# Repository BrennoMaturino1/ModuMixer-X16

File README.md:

# ModuMixer X16
ModuMixer is a modular digital audio mixer project with an almost unlimited amount of input and output channels (the limit is 65536)
It can be customized with input or output modules that are recognized by the "main computer"
The cue and main output signals are connected together in a summing amplifier configuration where each module sums it's signal to the data lines
The modules are digitally recognized by a custom protocol over USART where during boot one module is powered at a time and receives an address from the main computer (i know connecting multiple devices to USART isn't a good idea but i guess it will work), the digital signal processing works with an STM32 microcontroller for processing and a codec for digital to analog and analog to digital conversions

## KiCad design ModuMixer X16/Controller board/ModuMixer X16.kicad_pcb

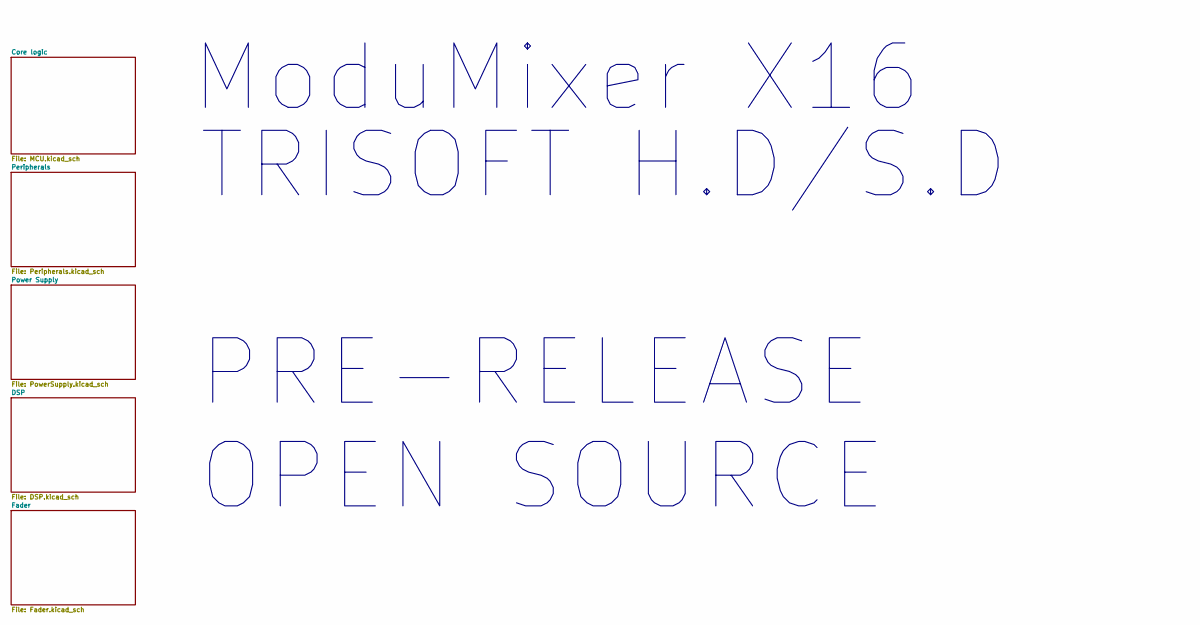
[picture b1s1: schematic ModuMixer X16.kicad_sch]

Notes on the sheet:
ModuMixer X16
TRISOFT H.D/S.D PRE-RELEASE OPEN SOURCE

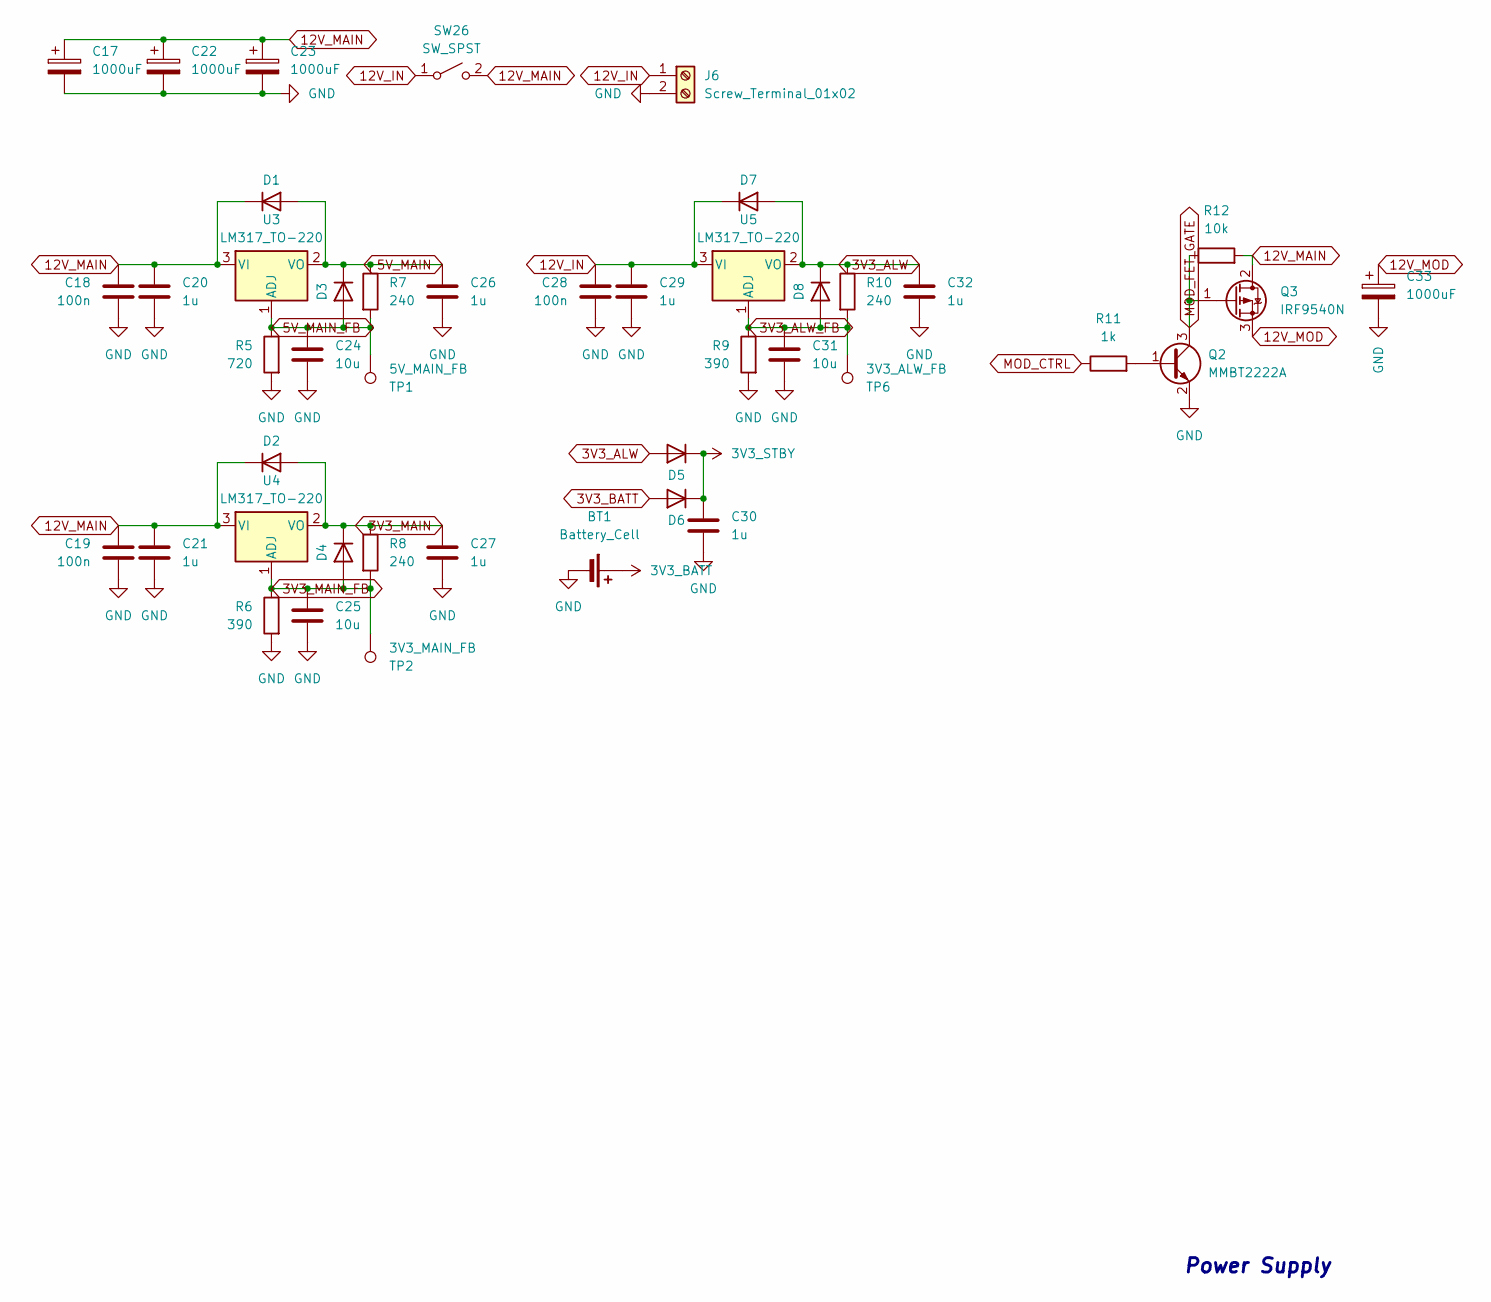
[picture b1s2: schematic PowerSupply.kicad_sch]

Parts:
BT1: Battery_Cell
C17, C22, C23, C33: 1000uF; CP_Elec_10x10
C18, C19, C28: 100n; C_0603_1608Metric
C20, C21, C26, C27, C29, C30, C32: 1u; C_0603_1608Metric
C24, C25, C31: 10u; C_0603_1608Metric
D1, D2, D3, D4, D5, D6, D7, D8: D_SOD-123
J6: Screw_Terminal_01x02; TerminalBlock_Xinya_XY308-2.54-2P_1x02_P2.54mm_Horizontal
Q2: MMBT2222A; SOT-23
Q3: IRF9540N; TO-220-3_Vertical
R5: 720; R_0603_1608Metric
R6, R9: 390; R_0603_1608Metric
R7, R8, R10: 240; R_0603_1608Metric
R11: 1k; R_0603_1608Metric
R12: 10k; R_0603_1608Metric
SW26: SW_SPST; TerminalBlock_Xinya_XY308-2.54-2P_1x02_P2.54mm_Horizontal
TP1: 5V_MAIN_FB; TestPoint_Pad_D3.0mm
TP2: 3V3_MAIN_FB; TestPoint_Pad_D3.0mm
TP6: 3V3_ALW_FB; TestPoint_Pad_D3.0mm
U3, U4, U5: LM317_TO-220; TO-220-3_Vertical

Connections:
3V3_ALW: C32.1, D5.2 (A), D7.2 (A), D8.1 (K), R10.1, U5.2 (VO)
3V3_ALW_FB: C31.1, D8.2 (A), R9.1, R10.2, TP6.1, U5.1 (ADJ)
3V3_BATT: D6.2 (A)
3V3_MAIN: C27.1, D2.2 (A), D4.1 (K), R8.1, U4.2 (VO); also elsewhere on the board
3V3_MAIN_FB: C25.1, D4.2 (A), R6.1, R8.2, TP2.1, U4.1 (ADJ)
3V3_STBY: C30.1, D5.1 (K), D6.1 (K); also elsewhere on the board
5V_MAIN: C26.1, D1.2 (A), D3.1 (K), R7.1, U3.2 (VO); also elsewhere on the board
5V_MAIN_FB: C24.1, D3.2 (A), R5.1, R7.2, TP1.1, U3.1 (ADJ)
12V_IN: C28.1, C29.1, D7.1 (K), J6.1, SW26.1 (A), U5.3 (VI)
12V_MAIN: C17.1, C18.1, C19.1, C20.1, C21.1, C22.1, C23.1, D1.1 (K), D2.1 (K), Q3.2 (D), R12.2, SW26.2 (B), U3.3 (VI), U4.3 (VI)
12V_MOD: C33.1, Q3.3 (S); also elsewhere on the board
GND: BT1.2 (-), C17.2, C18.2, C19.2, C20.2, C21.2, C22.2, C23.2, C24.2, C25.2, C26.2, C27.2, C28.2, C29.2, C30.2, C31.2, C32.2, C33.2, J6.2, Q2.2 (E), R5.2, R6.2, R9.2; also elsewhere on the board
MOD_CTRL: R11.1; also elsewhere on the board
MOD_FET_GATE: Q2.3 (C), Q3.1 (G), R12.1
unnamed: Q2.1 (B), R11.2

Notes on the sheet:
Power Supply

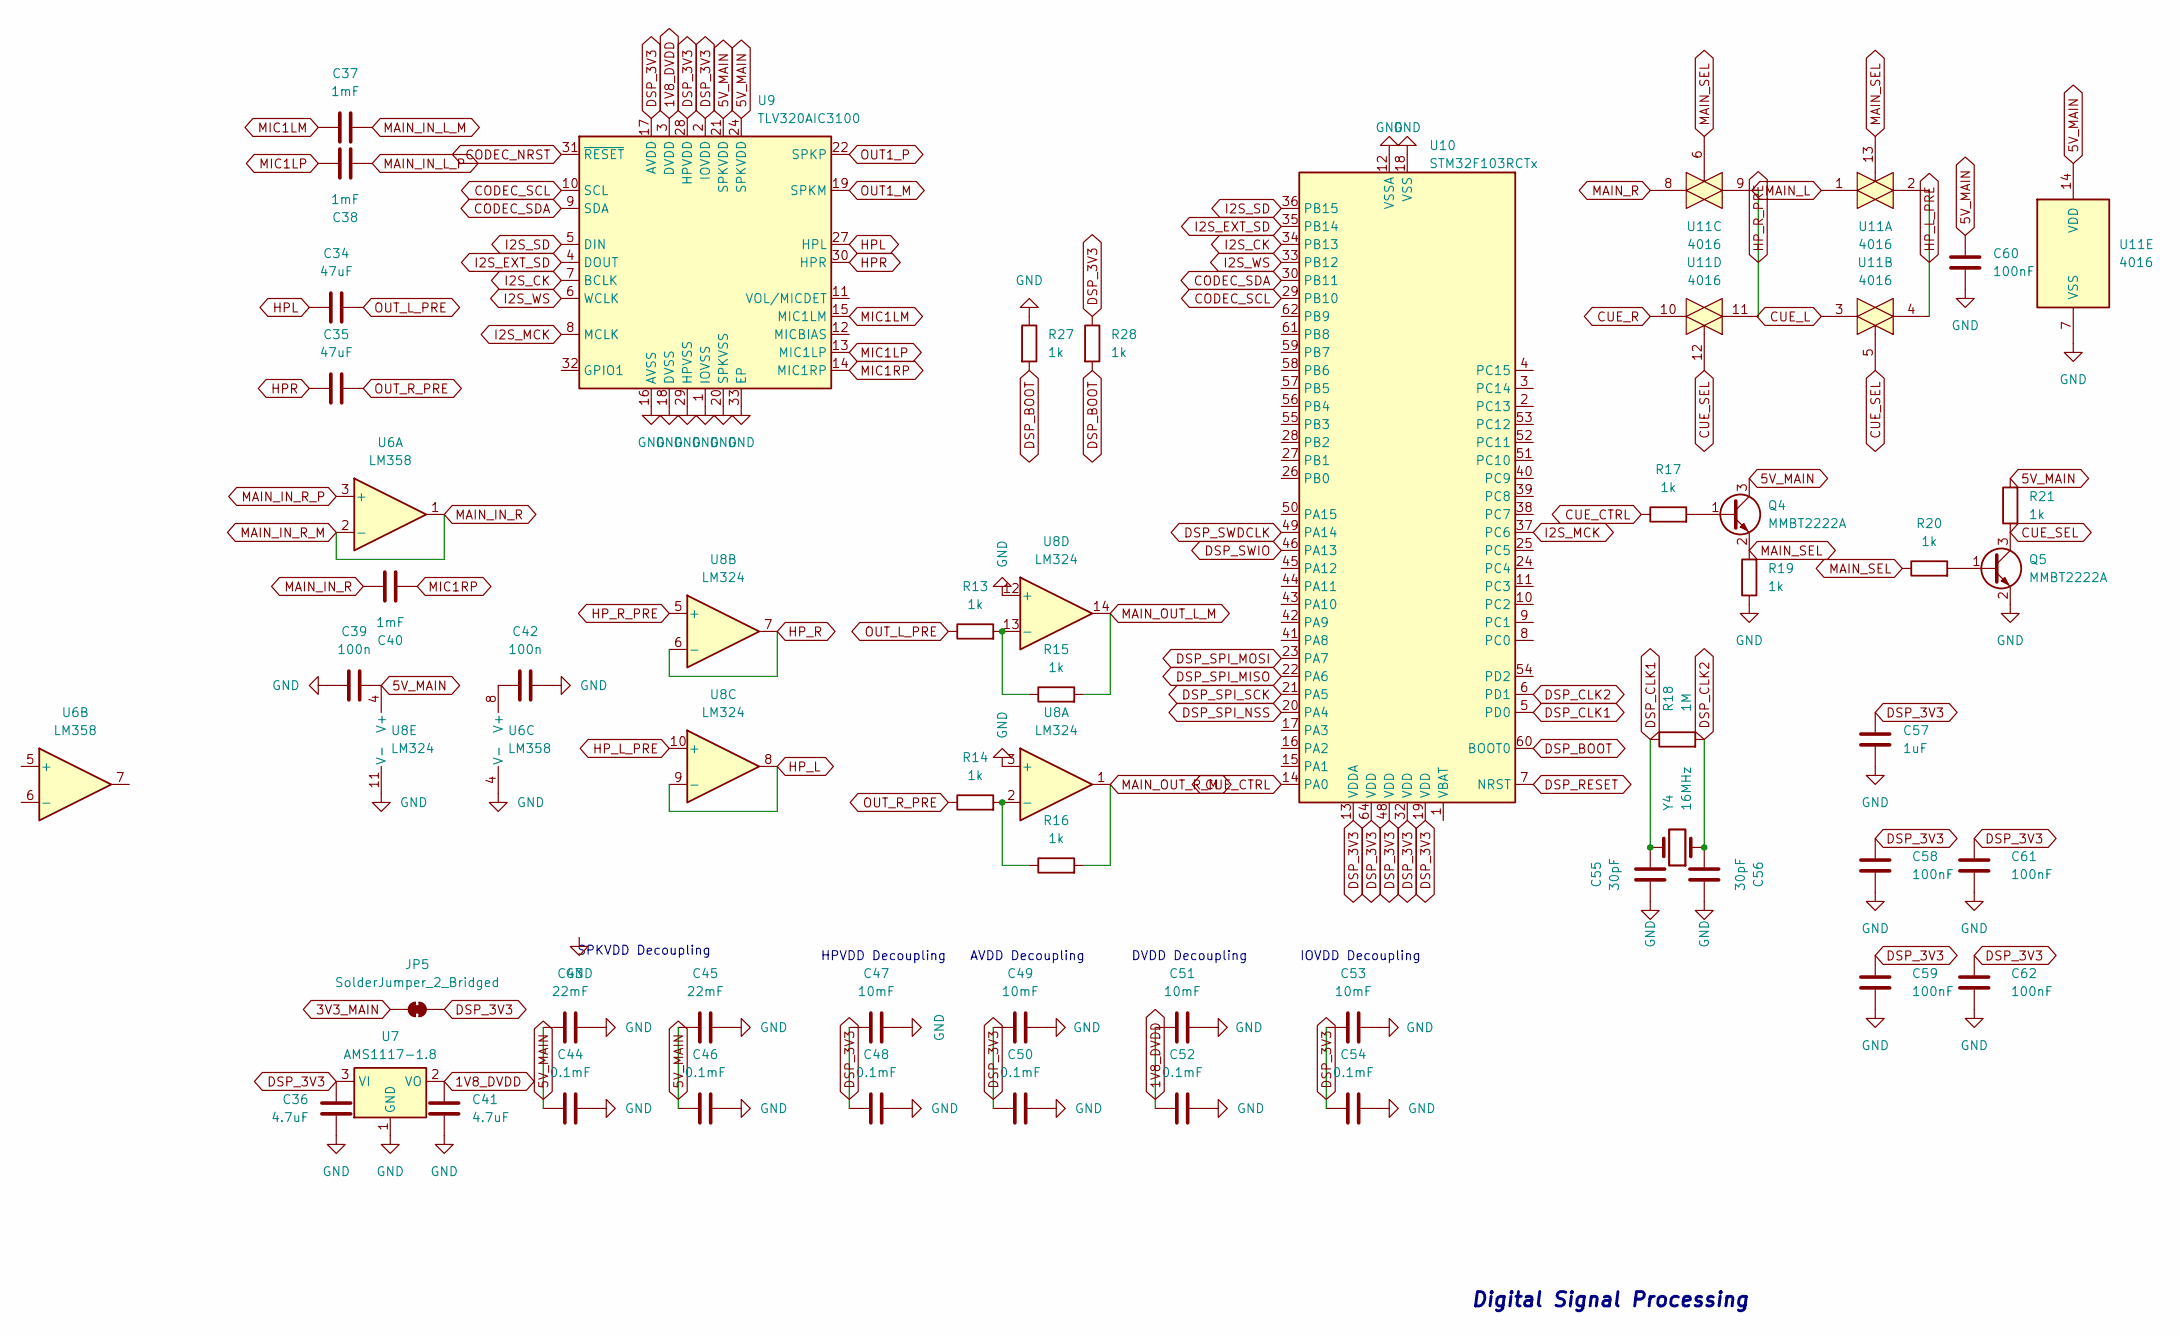
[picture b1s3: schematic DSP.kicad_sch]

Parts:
C34, C35: 47uF; C_0603_1608Metric
C36, C41: 4.7uF; C_0603_1608Metric
C37, C38, C40: 1mF; C_0603_1608Metric
C39, C42: 100n; C_0603_1608Metric
C43, C45: 22mF; C_0603_1608Metric
C44, C46, C48, C50, C52, C54: 0.1mF; C_0603_1608Metric
C47, C49, C51, C53: 10mF; C_0603_1608Metric
C55, C56: 30pF; C_0603_1608Metric
C57: 1uF; C_0603_1608Metric
C58, C59, C60, C61, C62: 100nF; C_0603_1608Metric
JP5: SolderJumper_2_Bridged; SolderJumper-2_P1.3mm_Bridged2Bar_Pad1.0x1.5mm
Q4, Q5: MMBT2222A; SOT-23
R13, R14, R15, R16, R17, R19, R20, R21, R27, R28: 1k; R_0603_1608Metric
R18: 1M; R_0603_1608Metric
U6: LM358; LFCSP-8_2x2mm_P0.5mm
U7: AMS1117-1.8; SOT-223-3_TabPin2
U8: LM324; SOIC-14_3.9x8.7mm_P1.27mm
U9: TLV320AIC3100; VQFN-32-1EP_5x5mm_P0.5mm_EP3.5x3.5mm
U10: STM32F103RCTx; LQFP-64_10x10mm_P0.5mm
U11: 4016; SOIC-14_3.9x8.7mm_P1.27mm
Y4: 16MHz; Crystal_HC49-U_Vertical

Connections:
1V8_DVDD: C41.2, C51.1, C52.1, U7.2 (VO), U9.3 (DVDD)
3V3_MAIN: JP5.1 (A); also elsewhere on the board
5V_MAIN: C39.2, C43.1, C44.1, C45.1, C46.1, C60.1, Q4.3 (C), R21.2, U8.4 (V+), U9.21 (SPKVDD), U9.24 (SPKVDD), U11.14 (VDD); also elsewhere on the board
CODEC_NRST: U9.31 (~RESET)
CODEC_SCL: U9.10 (SCL), U10.29 (PB10)
CODEC_SDA: U9.9 (SDA), U10.30 (PB11)
CUE_CTRL: R17.1, U10.14 (PA0)
CUE_L: U11.3
CUE_R: U11.10
CUE_SEL: Q5.3 (C), R21.1, U11.5, U11.12
DSP_3V3: C36.2, C47.1, C48.1, C49.1, C50.1, C53.1, C54.1, C57.1, C58.1, C59.1, C61.1, C62.1, JP5.2 (B), R28.1, U7.3 (VI), U9.2 (IOVDD), U9.17 (AVDD), U9.28 (HPVDD), U10.13 (VDDA), U10.19 (VDD), U10.32 (VDD), U10.48 (VDD), U10.64 (VDD)
DSP_BOOT: R27.2, R28.2, U10.60 (BOOT0); also elsewhere on the board
DSP_CLK1: C55.1, R18.1, U10.5 (PD0), Y4.2
DSP_CLK2: C56.1, R18.2, U10.6 (PD1), Y4.1
DSP_RESET: U10.7 (NRST); also elsewhere on the board
DSP_SPI_MISO: U10.22 (PA6)
DSP_SPI_MOSI: U10.23 (PA7)
DSP_SPI_NSS: U10.20 (PA4)
DSP_SPI_SCK: U10.21 (PA5)
DSP_SWDCLK: U10.49 (PA14); also elsewhere on the board
DSP_SWIO: U10.46 (PA13); also elsewhere on the board
GND: C36.1, C39.1, C41.1, C42.2, C43.2, C44.2, C45.2, C46.2, C47.2, C48.2, C49.2, C50.2, C51.2, C52.2, C53.2, C54.2, C55.2, C56.2, C57.2, C58.2, C59.2, C60.2, C61.2, C62.2, Q5.2 (E), R19.1, R27.1, U6.4 (V-), U7.1 (GND), U8.3 (+), U8.11 (V-), U8.12 (+), U9.1 (IOVSS), U9.16 (AVSS), U9.18 (DVSS), U9.20 (SPKVSS), U9.25 (SPKVSS), U9.29 (HPVSS), U9.33 (EP), U10.12 (VSSA), U10.18 (VSS), U10.31 (VSS), U10.47 (VSS), U10.63 (VSS), U11.7 (VSS); also elsewhere on the board
HPL: C34.1, U9.27 (HPL)
HPR: C35.1, U9.30 (HPR)
HP_L: U8.8, U8.9 (-); also elsewhere on the board
HP_L_PRE: U8.10 (+), U11.2, U11.4
HP_R: U8.6 (-), U8.7; also elsewhere on the board
HP_R_PRE: U8.5 (+), U11.9, U11.11
I2S_CK: U9.7 (BCLK), U10.34 (PB13)
I2S_EXT_SD: U9.4 (DOUT), U10.35 (PB14)
I2S_MCK: U9.8 (MCLK), U10.37 (PC6)
I2S_SD: U9.5 (DIN), U10.36 (PB15)
I2S_WS: U9.6 (WCLK), U10.33 (PB12)
MAIN_IN_L_M: C37.2
MAIN_IN_L_P: C38.2
MAIN_IN_R: C40.2, U6.1, U6.2 (-)
MAIN_IN_R_P: U6.3 (+)
MAIN_L: U11.1
MAIN_OUT_L_M: R15.2, U8.14; also elsewhere on the board
MAIN_OUT_R_M: R16.2, U8.1; also elsewhere on the board
MAIN_R: U11.8
MAIN_SEL: Q4.2 (E), R19.2, R20.1, U11.6, U11.13
MIC1LM: C37.1, U9.15 (MIC1LM)
MIC1LP: C38.1, U9.13 (MIC1LP)
MIC1RP: C40.1, U9.14 (MIC1RP)
unnamed: Q4.1 (B), R17.2
unnamed: Q5.1 (B), R20.2
unnamed: C42.1, U6.8 (V+)
unnamed: R14.2, R16.1, U8.2 (-)
unnamed: R13.2, R15.1, U8.13 (-)
OUT1_M: U9.19 (SPKM), U9.23 (SPKM)
OUT1_P: U9.22 (SPKP), U9.26 (SPKP)
OUT_L_PRE: C34.2, R13.1; also elsewhere on the board
OUT_R_PRE: C35.2, R14.1; also elsewhere on the board

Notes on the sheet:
DVDD Decoupling
IOVDD Decoupling
Digital Signal Processing
HPVDD Decoupling
AVDD Decoupling
SPKVDD Decoupling

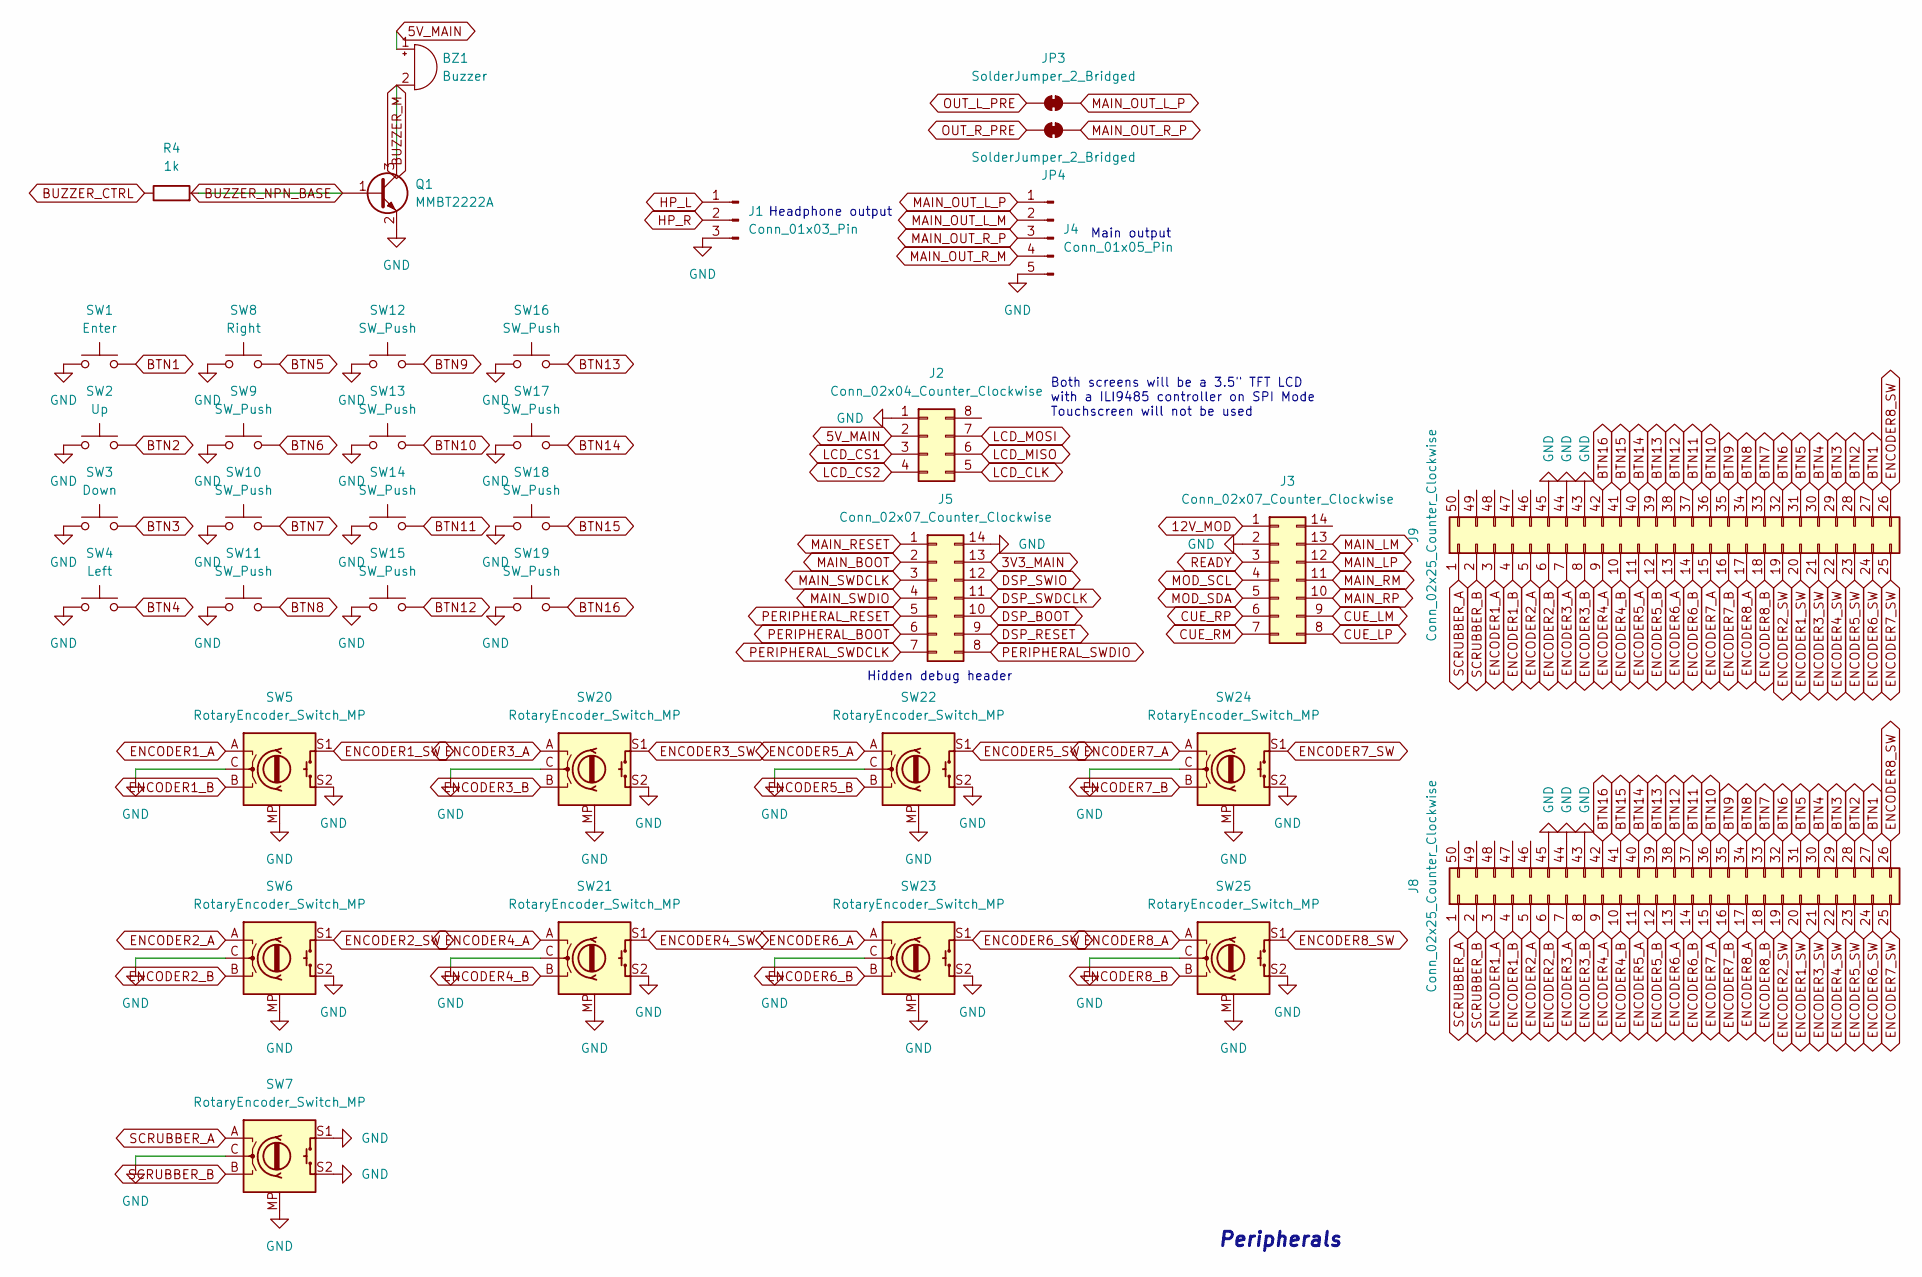
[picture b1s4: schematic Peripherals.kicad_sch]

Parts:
BZ1: Buzzer; Buzzer_12x9.5RM7.6
J1: Conn_01x03_Pin; PinHeader_1x03_P2.54mm_Vertical
J2: Conn_02x04_Counter_Clockwise; PinSocket_2x04_P2.54mm_Vertical
J3, J5: Conn_02x07_Counter_Clockwise; IDC-Header_2x07_P2.54mm_Vertical
J4: Conn_01x05_Pin; PinSocket_1x05_P2.54mm_Vertical
J8, J9: Conn_02x25_Counter_Clockwise; IDC-Header_2x25_P2.54mm_Vertical
JP3, JP4: SolderJumper_2_Bridged; SolderJumper-2_P1.3mm_Bridged2Bar_Pad1.0x1.5mm
Q1: MMBT2222A; SOT-23
R4: 1k; R_0603_1608Metric
SW1: Enter; SW_SPST_B3S-1000
SW2: Up; SW_SPST_B3S-1000
SW3: Down; SW_SPST_B3S-1000
SW4: Left; SW_SPST_B3S-1000
SW5, SW6, SW7, SW20, SW21, SW22, SW23, SW24, SW25: RotaryEncoder_Switch_MP; RotaryEncoder_Alps_EC11E-Switch_Vertical_H20mm
SW8: Right; SW_SPST_B3S-1000
SW9, SW10, SW11, SW12, SW13, SW14, SW15, SW16, SW17, SW18, SW19: SW_Push; SW_SPST_B3S-1000

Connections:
3V3_MAIN: J5.13; also elsewhere on the board
5V_MAIN: BZ1.1 (+), J2.2; also elsewhere on the board
12V_MOD: J3.1; also elsewhere on the board
BTN1: J8.27, J9.27, SW1.2; also elsewhere on the board
BTN2: J8.28, J9.28, SW2.2; also elsewhere on the board
BTN3: J8.29, J9.29, SW3.2; also elsewhere on the board
BTN4: J8.30, J9.30, SW4.2; also elsewhere on the board
BTN5: J8.31, J9.31, SW8.2; also elsewhere on the board
BTN6: J8.32, J9.32, SW9.2; also elsewhere on the board
BTN7: J8.33, J9.33, SW10.2; also elsewhere on the board
BTN8: J8.34, J9.34, SW11.2; also elsewhere on the board
BTN9: J8.35, J9.35, SW12.2; also elsewhere on the board
BTN10: J8.36, J9.36, SW13.2; also elsewhere on the board
BTN11: J8.37, J9.37, SW14.2; also elsewhere on the board
BTN12: J8.38, J9.38, SW15.2; also elsewhere on the board
BTN13: J8.39, J9.39, SW16.2; also elsewhere on the board
BTN14: J8.40, J9.40, SW17.2; also elsewhere on the board
BTN15: J8.41, J9.41, SW18.2; also elsewhere on the board
BTN16: J8.42, J9.42, SW19.2; also elsewhere on the board
BUZZER_CTRL: R4.1; also elsewhere on the board
BUZZER_M: BZ1.2 (-), Q1.3 (C)
BUZZER_NPN_BASE: Q1.1 (B), R4.2
CUE_LM: J3.9
CUE_LP: J3.8
CUE_RM: J3.7
CUE_RP: J3.6
DSP_BOOT: J5.10; also elsewhere on the board
DSP_RESET: J5.9; also elsewhere on the board
DSP_SWDCLK: J5.11; also elsewhere on the board
DSP_SWIO: J5.12; also elsewhere on the board
ENCODER1_A: J8.3, J9.3, SW5.A; also elsewhere on the board
ENCODER1_B: J8.4, J9.4, SW5.B; also elsewhere on the board
ENCODER1_SW: J8.20, J9.20, SW5.S1; also elsewhere on the board
ENCODER2_A: J8.5, J9.5, SW6.A; also elsewhere on the board
ENCODER2_B: J8.6, J9.6, SW6.B; also elsewhere on the board
ENCODER2_SW: J8.19, J9.19, SW6.S1; also elsewhere on the board
ENCODER3_A: J8.7, J9.7, SW20.A; also elsewhere on the board
ENCODER3_B: J8.8, J9.8, SW20.B; also elsewhere on the board
ENCODER3_SW: J8.21, J9.21, SW20.S1; also elsewhere on the board
ENCODER4_A: J8.9, J9.9, SW21.A; also elsewhere on the board
ENCODER4_B: J8.10, J9.10, SW21.B; also elsewhere on the board
ENCODER4_SW: J8.22, J9.22, SW21.S1; also elsewhere on the board
ENCODER5_A: J8.11, J9.11, SW22.A; also elsewhere on the board
ENCODER5_B: J8.12, J9.12, SW22.B; also elsewhere on the board
ENCODER5_SW: J8.23, J9.23, SW22.S1; also elsewhere on the board
ENCODER6_A: J8.13, J9.13, SW23.A; also elsewhere on the board
ENCODER6_B: J8.14, J9.14, SW23.B; also elsewhere on the board
ENCODER6_SW: J8.24, J9.24, SW23.S1; also elsewhere on the board
ENCODER7_A: J8.15, J9.15, SW24.A; also elsewhere on the board
ENCODER7_B: J8.16, J9.16, SW24.B; also elsewhere on the board
ENCODER7_SW: J8.25, J9.25, SW24.S1; also elsewhere on the board
ENCODER8_A: J8.17, J9.17, SW25.A; also elsewhere on the board
ENCODER8_B: J8.18, J9.18, SW25.B; also elsewhere on the board
ENCODER8_SW: J8.26, J9.26, SW25.S1; also elsewhere on the board
GND: J1.3, J2.1, J3.2, J4.5, J5.14, J8.43, J8.44, J8.45, J9.43, J9.44, J9.45, Q1.2 (E), SW1.1, SW2.1, SW3.1, SW4.1, SW5.C, SW5.MP, SW5.S2, SW6.C, SW6.MP, SW6.S2, SW7.C, SW7.MP, SW7.S1, SW7.S2, SW8.1, SW9.1, SW10.1, SW11.1, SW12.1, SW13.1, SW14.1, SW15.1, SW16.1, SW17.1, SW18.1, SW19.1, SW20.C, SW20.MP, SW20.S2, SW21.C, SW21.MP, SW21.S2, SW22.C, SW22.MP, SW22.S2, SW23.C, SW23.MP, SW23.S2, SW24.C, SW24.MP, SW24.S2, SW25.C, SW25.MP, SW25.S2; also elsewhere on the board
HP_L: J1.1; also elsewhere on the board
HP_R: J1.2; also elsewhere on the board
LCD_CLK: J2.5; also elsewhere on the board
LCD_CS1: J2.3; also elsewhere on the board
LCD_CS2: J2.4; also elsewhere on the board
LCD_MISO: J2.6; also elsewhere on the board
LCD_MOSI: J2.7; also elsewhere on the board
MAIN_BOOT: J5.2; also elsewhere on the board
MAIN_LM: J3.13
MAIN_LP: J3.12
MAIN_OUT_L_M: J4.2; also elsewhere on the board
MAIN_OUT_L_P: J4.1, JP3.2 (B)
MAIN_OUT_R_M: J4.4; also elsewhere on the board
MAIN_OUT_R_P: J4.3, JP4.1 (A)
MAIN_RESET: J5.1; also elsewhere on the board
MAIN_RM: J3.11
MAIN_RP: J3.10
MAIN_SWDCLK: J5.3; also elsewhere on the board
MAIN_SWDIO: J5.4; also elsewhere on the board
MOD_SCL: J3.4; also elsewhere on the board
MOD_SDA: J3.5; also elsewhere on the board
OUT_L_PRE: JP3.1 (A); also elsewhere on the board
OUT_R_PRE: JP4.2 (B); also elsewhere on the board
PERIPHERAL_BOOT: J5.6; also elsewhere on the board
PERIPHERAL_RESET: J5.5; also elsewhere on the board
PERIPHERAL_SWDCLK: J5.7; also elsewhere on the board
PERIPHERAL_SWDIO: J5.8; also elsewhere on the board
READY: J3.3
SCRUBBER_A: J8.1, J9.1, SW7.A; also elsewhere on the board
SCRUBBER_B: J8.2, J9.2, SW7.B; also elsewhere on the board

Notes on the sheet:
Main output
Headphone output
Hidden debug header
Both screens will be a 3.5" TFT LCD with a ILI9485 controller on SPI Mode Touchscreen will not be used
Peripherals

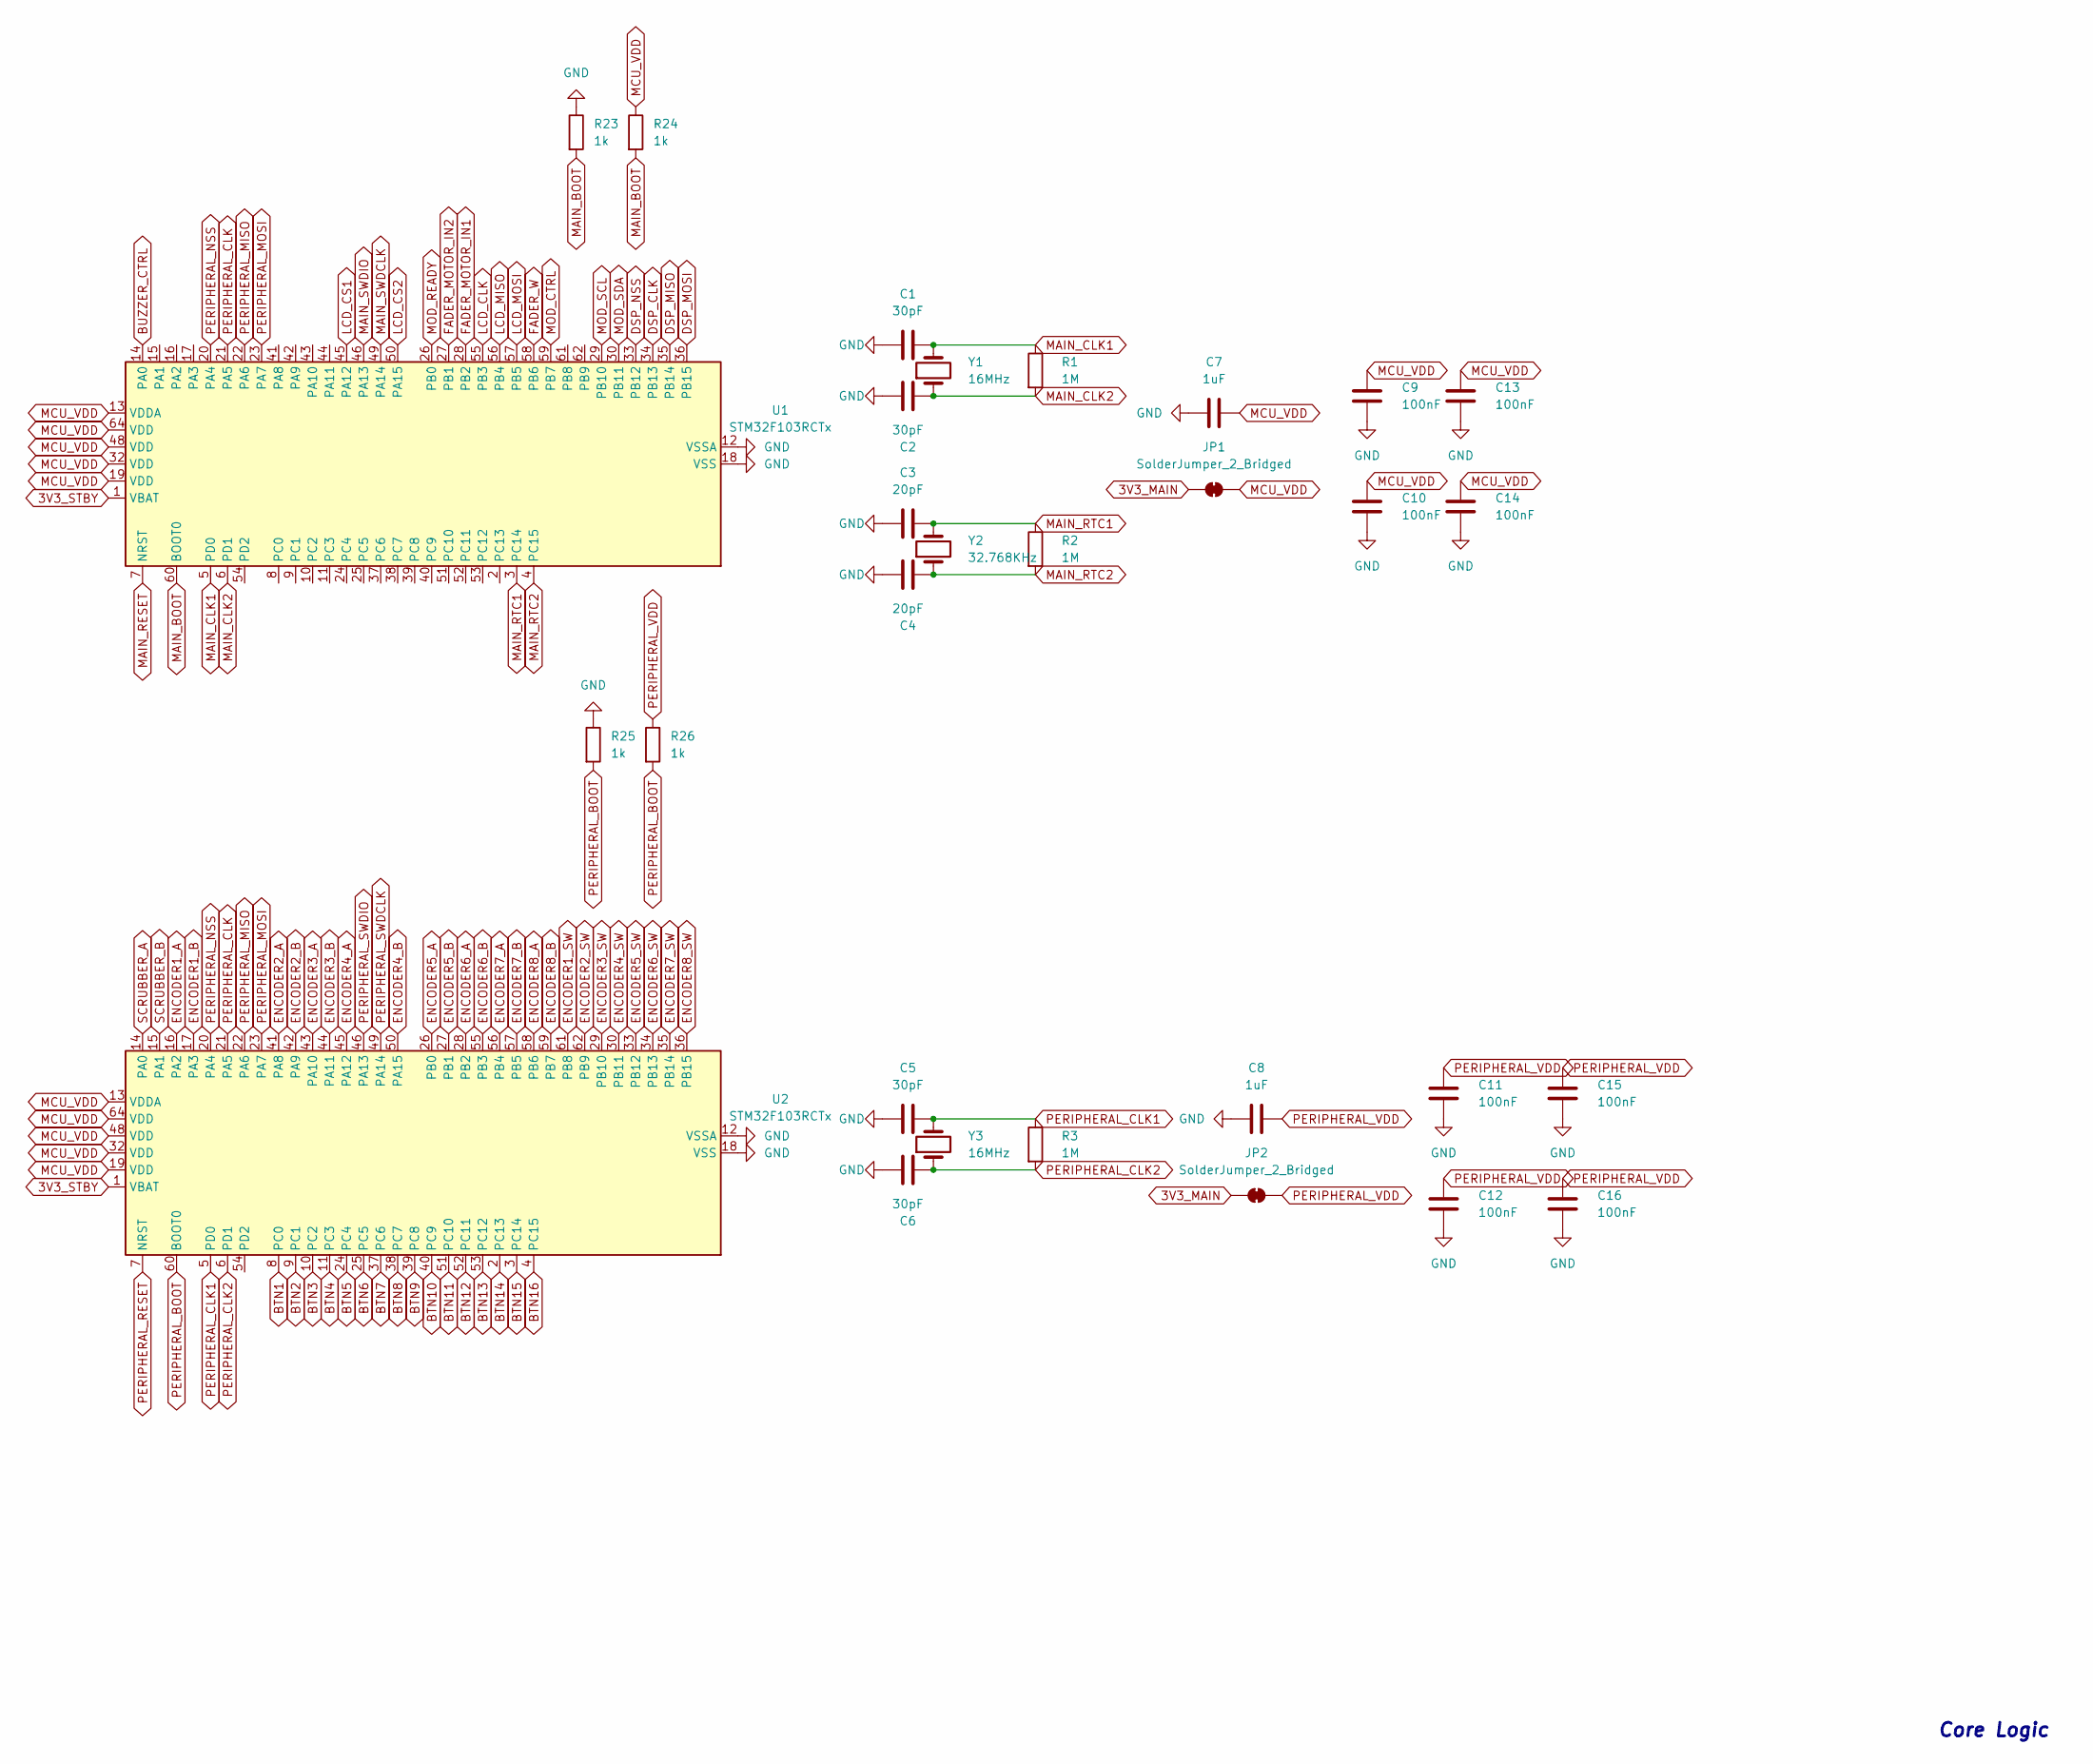
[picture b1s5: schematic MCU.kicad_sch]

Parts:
C1, C2, C5, C6: 30pF; C_0603_1608Metric
C3, C4: 20pF; C_0603_1608Metric
C7, C8: 1uF; C_0603_1608Metric
C9, C10, C11, C12, C13, C14, C15, C16: 100nF; C_0603_1608Metric
JP1, JP2: SolderJumper_2_Bridged; SolderJumper-2_P1.3mm_Bridged2Bar_Pad1.0x1.5mm
R1, R2, R3: 1M; R_0603_1608Metric
R23, R24, R25, R26: 1k; R_0603_1608Metric
U1, U2: STM32F103RCTx; LQFP-64_10x10mm_P0.5mm
Y1, Y3: 16MHz; Crystal_HC49-U_Vertical
Y2: 32.768KHz; Crystal_HC49-U_Vertical

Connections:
3V3_MAIN: JP1.1 (A), JP2.1 (A); also elsewhere on the board
3V3_STBY: U1.1 (VBAT), U2.1 (VBAT); also elsewhere on the board
BTN1: U2.8 (PC0); also elsewhere on the board
BTN2: U2.9 (PC1); also elsewhere on the board
BTN3: U2.10 (PC2); also elsewhere on the board
BTN4: U2.11 (PC3); also elsewhere on the board
BTN5: U2.24 (PC4); also elsewhere on the board
BTN6: U2.25 (PC5); also elsewhere on the board
BTN7: U2.37 (PC6); also elsewhere on the board
BTN8: U2.38 (PC7); also elsewhere on the board
BTN9: U2.39 (PC8); also elsewhere on the board
BTN10: U2.40 (PC9); also elsewhere on the board
BTN11: U2.51 (PC10); also elsewhere on the board
BTN12: U2.52 (PC11); also elsewhere on the board
BTN13: U2.53 (PC12); also elsewhere on the board
BTN14: U2.2 (PC13); also elsewhere on the board
BTN15: U2.3 (PC14); also elsewhere on the board
BTN16: U2.4 (PC15); also elsewhere on the board
BUZZER_CTRL: U1.14 (PA0); also elsewhere on the board
DSP_CLK: U1.34 (PB13)
DSP_MISO: U1.35 (PB14)
DSP_MOSI: U1.36 (PB15)
DSP_NSS: U1.33 (PB12)
ENCODER1_A: U2.16 (PA2); also elsewhere on the board
ENCODER1_B: U2.17 (PA3); also elsewhere on the board
ENCODER1_SW: U2.61 (PB8); also elsewhere on the board
ENCODER2_A: U2.41 (PA8); also elsewhere on the board
ENCODER2_B: U2.42 (PA9); also elsewhere on the board
ENCODER2_SW: U2.62 (PB9); also elsewhere on the board
ENCODER3_A: U2.43 (PA10); also elsewhere on the board
ENCODER3_B: U2.44 (PA11); also elsewhere on the board
ENCODER3_SW: U2.29 (PB10); also elsewhere on the board
ENCODER4_A: U2.45 (PA12); also elsewhere on the board
ENCODER4_B: U2.50 (PA15); also elsewhere on the board
ENCODER4_SW: U2.30 (PB11); also elsewhere on the board
ENCODER5_A: U2.26 (PB0); also elsewhere on the board
ENCODER5_B: U2.27 (PB1); also elsewhere on the board
ENCODER5_SW: U2.33 (PB12); also elsewhere on the board
ENCODER6_A: U2.28 (PB2); also elsewhere on the board
ENCODER6_B: U2.55 (PB3); also elsewhere on the board
ENCODER6_SW: U2.34 (PB13); also elsewhere on the board
ENCODER7_A: U2.56 (PB4); also elsewhere on the board
ENCODER7_B: U2.57 (PB5); also elsewhere on the board
ENCODER7_SW: U2.35 (PB14); also elsewhere on the board
ENCODER8_A: U2.58 (PB6); also elsewhere on the board
ENCODER8_B: U2.59 (PB7); also elsewhere on the board
ENCODER8_SW: U2.36 (PB15); also elsewhere on the board
FADER_MOTOR_IN1: U1.28 (PB2); also elsewhere on the board
FADER_MOTOR_IN2: U1.27 (PB1); also elsewhere on the board
FADER_W: U1.58 (PB6); also elsewhere on the board
GND: C1.2, C2.2, C3.2, C4.2, C5.2, C6.2, C7.1, C8.1, C9.2, C10.2, C11.2, C12.2, C13.2, C14.2, C15.2, C16.2, R23.1, R25.1, U1.12 (VSSA), U1.18 (VSS), U1.31 (VSS), U1.47 (VSS), U1.63 (VSS), U2.12 (VSSA), U2.18 (VSS), U2.31 (VSS), U2.47 (VSS), U2.63 (VSS); also elsewhere on the board
LCD_CLK: U1.55 (PB3); also elsewhere on the board
LCD_CS1: U1.45 (PA12); also elsewhere on the board
LCD_CS2: U1.50 (PA15); also elsewhere on the board
LCD_MISO: U1.56 (PB4); also elsewhere on the board
LCD_MOSI: U1.57 (PB5); also elsewhere on the board
MAIN_BOOT: R23.2, R24.2, U1.60 (BOOT0); also elsewhere on the board
MAIN_CLK1: C1.1, R1.1, U1.5 (PD0), Y1.2
MAIN_CLK2: C2.1, R1.2, U1.6 (PD1), Y1.1
MAIN_RESET: U1.7 (NRST); also elsewhere on the board
MAIN_RTC1: C3.1, R2.1, U1.3 (PC14), Y2.2
MAIN_RTC2: C4.1, R2.2, U1.4 (PC15), Y2.1
MAIN_SWDCLK: U1.49 (PA14); also elsewhere on the board
MAIN_SWDIO: U1.46 (PA13); also elsewhere on the board
MCU_VDD: C7.2, C9.1, C10.1, C13.1, C14.1, JP1.2 (B), R24.1, U1.13 (VDDA), U1.19 (VDD), U1.32 (VDD), U1.48 (VDD), U1.64 (VDD), U2.13 (VDDA), U2.19 (VDD), U2.32 (VDD), U2.48 (VDD), U2.64 (VDD)
MOD_CTRL: U1.59 (PB7); also elsewhere on the board
MOD_READY: U1.26 (PB0)
MOD_SCL: U1.29 (PB10); also elsewhere on the board
MOD_SDA: U1.30 (PB11); also elsewhere on the board
PERIPHERAL_BOOT: R25.2, R26.2, U2.60 (BOOT0); also elsewhere on the board
PERIPHERAL_CLK: U1.21 (PA5), U2.21 (PA5)
PERIPHERAL_CLK1: C5.1, R3.1, U2.5 (PD0), Y3.2
PERIPHERAL_CLK2: C6.1, R3.2, U2.6 (PD1), Y3.1
PERIPHERAL_MISO: U1.22 (PA6), U2.22 (PA6)
PERIPHERAL_MOSI: U1.23 (PA7), U2.23 (PA7)
PERIPHERAL_NSS: U1.20 (PA4), U2.20 (PA4)
PERIPHERAL_RESET: U2.7 (NRST); also elsewhere on the board
PERIPHERAL_SWDCLK: U2.49 (PA14); also elsewhere on the board
PERIPHERAL_SWDIO: U2.46 (PA13); also elsewhere on the board
PERIPHERAL_VDD: C8.2, C11.1, C12.1, C15.1, C16.1, JP2.2 (B), R26.1
SCRUBBER_A: U2.14 (PA0); also elsewhere on the board
SCRUBBER_B: U2.15 (PA1); also elsewhere on the board

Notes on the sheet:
Core Logic
